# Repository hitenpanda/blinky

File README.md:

---
Title: Blinky
Author: Hiten Panda
Description: An LED chaser circuit using ICs only.
Created at: 2026-04-18
---
# Blinky - An LED chaser circuit using ICs only.
**The ICs used are:**
| Serial No.               | Part Name              | Purpose                 |
|:-------------------------|:----------------------:|:-----------------------:|
|1                         |NE555P                  | It acts as a clock.     |
|2                         |CD4017BE                  | It acts as a counter.     |

I was curious to learn about how some ICs work, thought of learning by making one.

Took some screenshot while making the project. It was a fun project to work with ICs and help me understand how do they work.

## Parts List:
These are the parts I used for making it:
| Serial No.               | Part Name              | Quantity                |
|:-------------------------|:----------------------:|:-----------------------:|
| 1                        | 100uF 25V Cap          | 1                       |
| 2                        | NE555P                 | 1                       |
| 3                        | CD4017BE               | 1                       |
| 4                        | W104 Trim Pot 100k Ohm | 1                       |
| 5                        | 1k Ohm Resistor        | 1                       |
| 6                        | 470 Ohm Resistor       | 1                       |
| 7                        | 0.1uF Disc Cap         | 1                       |
| 8                        | Header Pin             | 2                       |
| 9                        | Through-Hole LED       | 10                      |

## Screenshots I took:
**In between the schematics process:**
[!between-schematics](Images/Screenshot-50.png)

**After completing schematics:**
[!after-schematics](Images/Screenshot-51.png)

**After completing the PCB:**
[!after-pcb](Images/Screenshot-52.png)

**3D-Render of the PCB:**
[!render](Images/Screenshot-53.png)

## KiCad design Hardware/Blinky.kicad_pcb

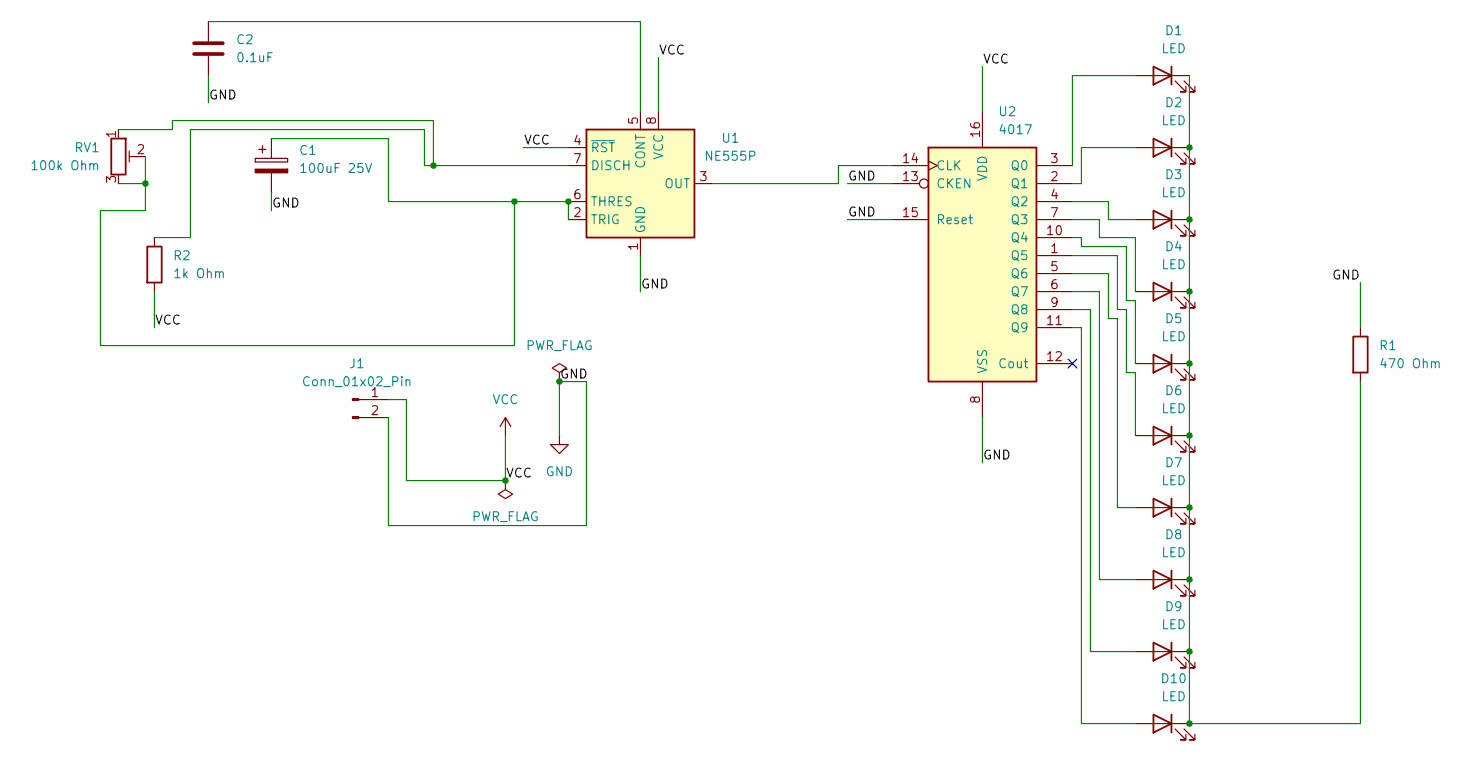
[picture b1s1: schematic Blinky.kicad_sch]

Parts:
C1: 100uF 25V; CP_Radial_D6.3mm_P2.50mm
C2: 0.1uF; C_Disc_D5.0mm_W2.5mm_P2.50mm
D1, D2, D3, D4, D5, D6, D7, D8, D9, D10: LED; LED_D5.0mm
J1: Conn_01x02_Pin; PinHeader_1x02_P2.54mm_Vertical
R1: 470 Ohm; R_Axial_DIN0207_L6.3mm_D2.5mm_P7.62mm_Horizontal
R2: 1k Ohm; R_Axial_DIN0207_L6.3mm_D2.5mm_P7.62mm_Horizontal
RV1: 100k Ohm; Potentiometer_Bourns_3296W_Vertical
U1: NE555P; DIP-8_W7.62mm
U2: 4017; DIP-16_W7.62mm

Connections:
GND: C1.2, C2.2, J1.2, R1.1, U1.1 (GND), U2.8 (VSS), U2.13 (CKEN), U2.15 (Reset)
unnamed: D1.2 (A), U2.3 (Q0)
unnamed: D1.1 (K), D2.1 (K), D3.1 (K), D4.1 (K), D5.1 (K), D6.1 (K), D7.1 (K), D8.1 (K), D9.1 (K), D10.1 (K), R1.2
unnamed: D2.2 (A), U2.2 (Q1)
unnamed: D3.2 (A), U2.4 (Q2)
unnamed: D4.2 (A), U2.7 (Q3)
unnamed: D5.2 (A), U2.10 (Q4)
unnamed: D6.2 (A), U2.1 (Q5)
unnamed: D7.2 (A), U2.5 (Q6)
unnamed: D8.2 (A), U2.6 (Q7)
unnamed: D9.2 (A), U2.9 (Q8)
unnamed: D10.2 (A), U2.11 (Q9)
unnamed: C2.1, U1.5 (CONT)
unnamed: R2.1, RV1.1, U1.7 (DISCH)
unnamed: U1.3 (OUT), U2.14 (CLK)
unnamed: C1.1, RV1.2, RV1.3, U1.2 (TRIG), U1.6 (THRES)
VCC: J1.1, R2.2, U1.4 (~RST), U1.8 (VCC), U2.16 (VDD)

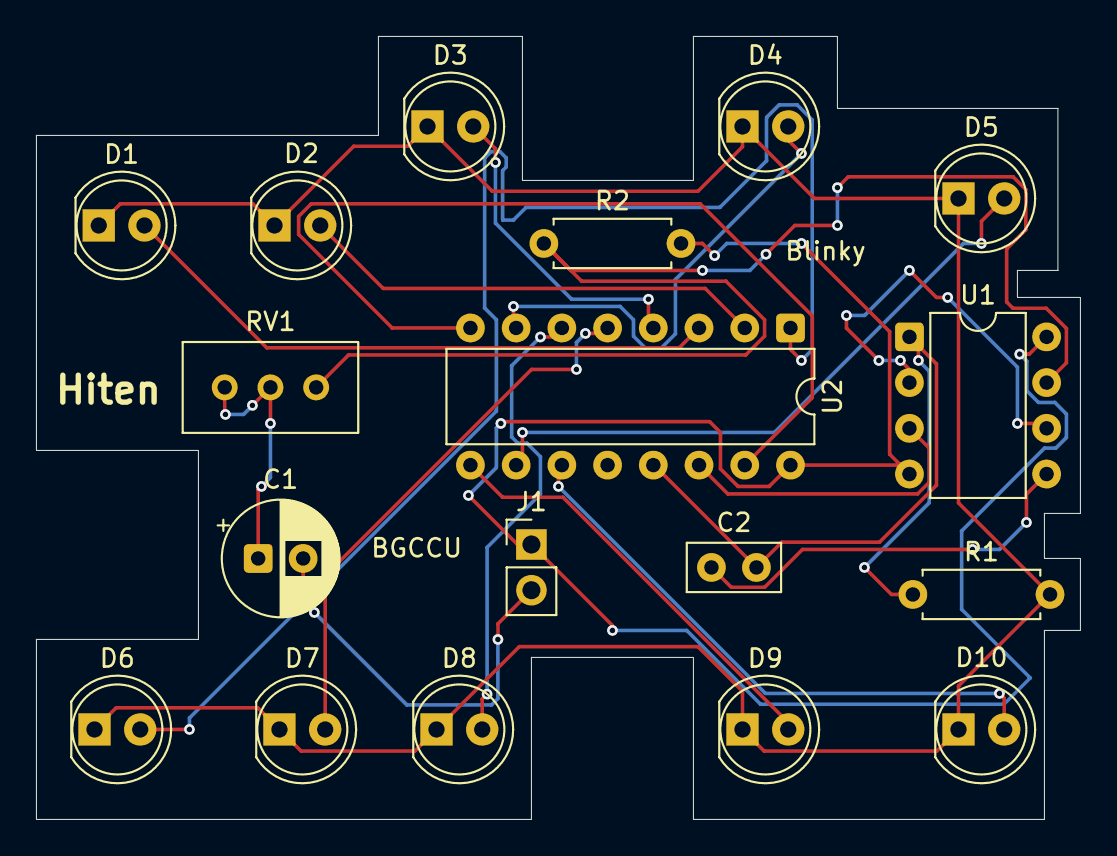
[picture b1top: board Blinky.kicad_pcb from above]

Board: 2 copper layers, 58.0 x 43.5 mm, 18 parts (0 on the bottom side), 17 nets.

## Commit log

2026-04-18 Complete Blinky design Done
